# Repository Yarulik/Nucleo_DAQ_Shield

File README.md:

# Nucleo DAQ Shield
The Nucleo DAQ Shield mixed signal PCB that houses connectors and auxiliary circuitry (buffers, H-bridge, voltage regulators). It allows the STM32 microcontroller to interface with the [Analog Frontend](https://github.com/ColumbiaOpenSourceUltrasound/Analog_Frontend), motor, and other sensors.

### Drawings
Schematic:  
  
See the `drawings` folder for a high-resolution PDF version.

PCB:  
  
See the `drawings` folder for a full resolution PDF version, including each layer individually. 

3D view:  

### Bill of Materials
See `Nucleo_DAQ_Shield.html`.

### Changelog
* `v1.0` Initial design.
* `v1.2` 
* `v1.3` Changed dimensions to improve manufacturability.
* `v2.0` Replaced several components; added connector for IMU and jumpers to switch between internal/external encoder.

### Credits
Designed by William Meng and Ruoyu Sheng.

The motor control circuitry was adapted from the [Adafruit DRV8871 breakout board](https://learn.adafruit.com/adafruit-drv8871-brushed-dc-motor-driver-breakout/download).

The [Arduino Shield module](https://www.thingiverse.com/thing:9630) by nicholasclewis helped with aligning the header pins.

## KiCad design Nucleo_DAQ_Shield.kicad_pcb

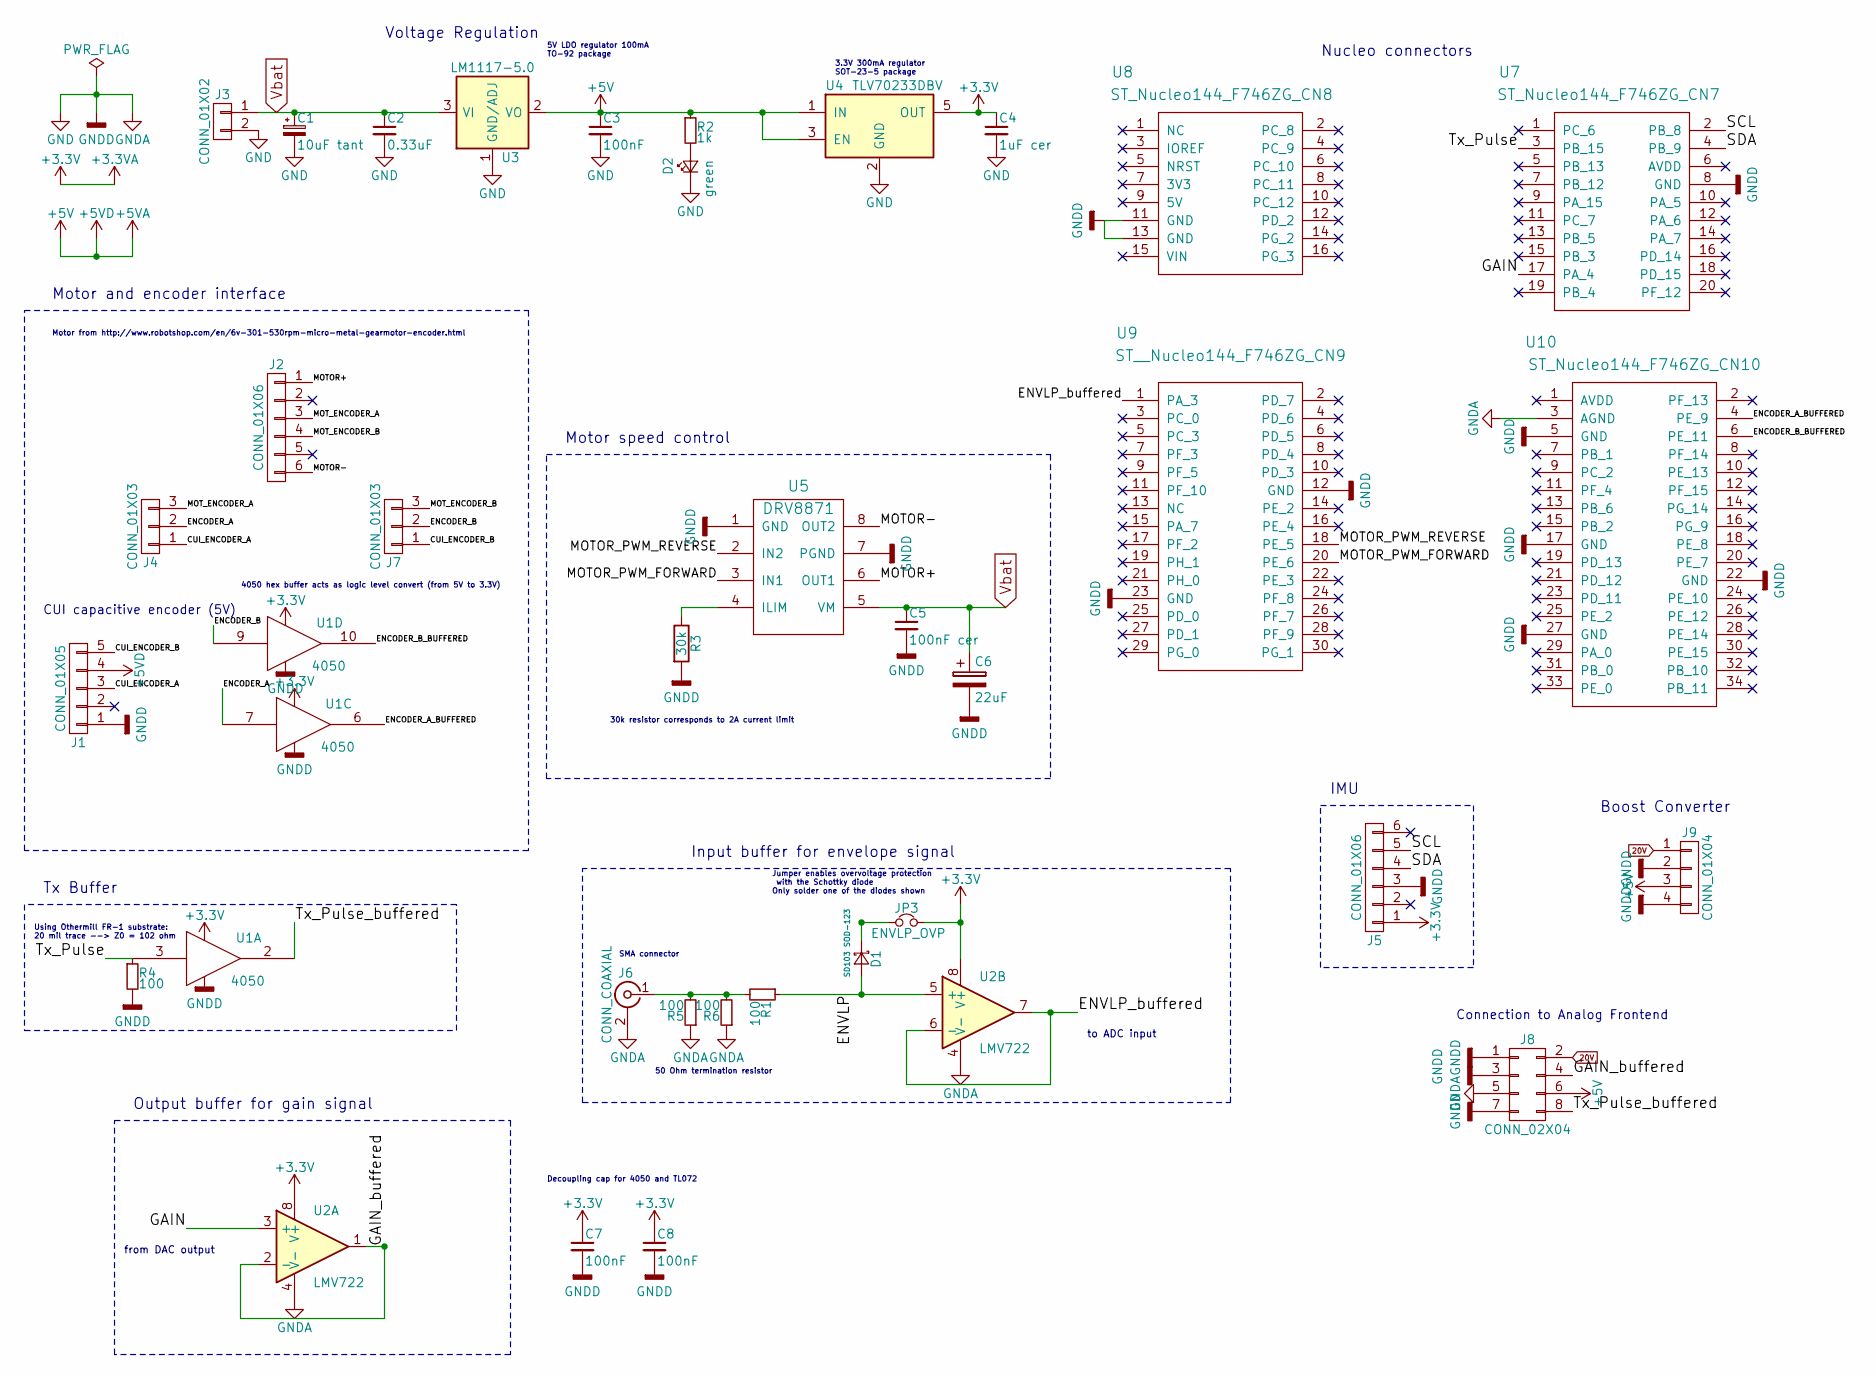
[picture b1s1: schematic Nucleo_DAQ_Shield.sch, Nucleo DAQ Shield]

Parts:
C1: 10uF tant; CP_Tantalum_Case-A_EIA-3216-18_Reflow
C2: 0.33uF; C_0603
C3, C7, C8: 100nF; C_0603
C4: 1uF cer; C_0603
C5: 100nF cer; C_0603
C6: 22uF; CP_Elec_6.3x5.8
D1: SD103 SOD-123; D_SOD-123
D2: green; LED_1206
J1: CONN_01X05; Pin_Header_Straight_1x05_Pitch2.54mm
J2, J5: CONN_01X06; Pin_Header_Straight_1x06_Pitch2.54mm
J3: CONN_01X02; Pin_Header_Straight_1x02_Pitch2.54mm
J4, J7: CONN_01X03; Pin_Header_Straight_1x03_Pitch2.54mm
J6: CONN_COAXIAL; SMA_uxcell
J8: CONN_02X04; Pin_Header_Straight_2x04_Pitch2.54mm
J9: CONN_01X04; Pin_Header_Straight_1x04_Pitch2.54mm
JP3: ENVLP_OVP; Pin_Header_Straight_1x02_Pitch2.54mm
R1, R4, R5, R6: 100; R_0805
R2: 1k; R_0805
R3: 30k; R_0805
U1: 4050; SOIC-16_3.9x9.9mm_Pitch1.27mm
U2: LMV722; SOIC-8_3.9x4.9mm_Pitch1.27mm
U3: LM1117-5.0; SOT-223
U4: TLV70233DBV; SOT-23-5
U5: DRV8871; SOIC-8_PowerPad
U7: ST_Nucleo144_F746ZG_CN7; Pin_Header_Straight_2x10_Pitch2.54mm
U8: ST_Nucleo144_F746ZG_CN8; Pin_Header_Straight_2x08_Pitch2.54mm
U9: ST__Nucleo144_F746ZG_CN9; Pin_Header_Straight_2x15_Pitch2.54mm
U10: ST_Nucleo144_F746ZG_CN10; Pin_Header_Straight_2x17_Pitch2.54mm

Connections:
20V: J8.2, J9.1
+3.3VA: C4.1, C7.1, C8.1, J5.1, JP3.2, U1.1 (VCC), U2.8 (V+), U4.5 (OUT)
+5V: C3.1, J1.4, J8.6, J9.3, R2.1, U3.2 (VO), U3.4 (VO), U4.1 (IN), U4.3 (EN)
/CUI_ENCODER_A: J1.3, J4.1
/CUI_ENCODER_B: J1.5, J7.1
/ENCODER_A: J4.2, U1.7
/ENCODER_A_BUFFERED: U1.6, U10.4 (PE_9)
/ENCODER_B: J7.2, U1.9
/ENCODER_B_BUFFERED: U1.10, U10.6 (PE_11)
/ENVLP: D1.2 (A), R1.1, U2.5 (+)
/ENVLP_buffered: U2.6 (-), U2.7, U9.1 (PA_3)
/GAIN: U2.3 (+), U7.17 (PA_4)
/GAIN_buffered: J8.4, U2.1, U2.2 (-)
/MOTOR+: J2.1, U5.6 (OUT1)
/MOTOR-: J2.6, U5.8 (OUT2)
/MOTOR_PWM_FORWARD: U5.3 (IN1), U9.20 (PE_6)
/MOTOR_PWM_REVERSE: U5.2 (IN2), U9.18 (PE_5)
/MOT_ENCODER_A: J2.3, J4.3
/MOT_ENCODER_B: J2.4, J7.3
/SCL: J5.5, U7.2 (PB_8)
/SDA: J5.4, U7.4 (PB_9)
/Tx_Pulse: R4.1, U1.3, U7.3 (PB_15)
/Tx_Pulse_buffered: J8.8, U1.2
GND: C1.2, C2.2, C3.2, C4.2, C5.2, C6.2, C7.2, C8.2, D2.1 (K), J1.1, J3.2, J5.3, J6.2 (Ext), J8.1, J8.3, J8.5, J8.7, J9.2, J9.4, R3.2, R4.2, R5.1, R6.1, U1.8 (VSS), U2.4 (V-), U3.1 (GND/ADJ), U4.2 (GND), U5.1 (GND), U5.7 (PGND), U7.8 (GND), U8.11 (GND), U8.13 (GND), U9.12 (GND), U9.23 (GND), U10.3 (AGND), U10.5 (GND), U10.17 (GND), U10.22 (GND), U10.27 (GND)
unnamed: D1.1 (K), JP3.1
unnamed: D2.2 (A), R2.2
unnamed: J6.1 (In), R1.2, R5.2, R6.2
unnamed: R3.1, U5.4 (ILIM)
Vbat: C1.1, C2.1, C5.1, C6.1, J3.1, U3.3 (VI), U5.5 (VM)

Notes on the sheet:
Output buffer for gain signal
Input buffer for envelope signal
from DAC output
to ADC input
Motor from http://www.robotshop.com/en/6v-301-530rpm-micro-metal-gearmotor-encoder.html
CUI capacitive encoder (5V)
3.3V 300mA regulator SOT-23-5 package
Motor speed control
Nucleo connectors
Jumper enables overvoltage protection with the Schottky diode Only solder one of the diodes shown
Motor and encoder interface
50 Ohm termination resistor
4050 hex buffer acts as logic level convert (from 5V to 3.3V)
30k resistor corresponds to 2A current limit
Tx Buffer
Voltage Regulation
Decoupling cap for 4050 and TL072
Using Othermill FR-1 substrate: 20 mil trace --> Z0 = 102 ohm
SMA connector
5V LDO regulator 100mA TO-92 package
IMU
Boost Converter
Connection to Analog Frontend

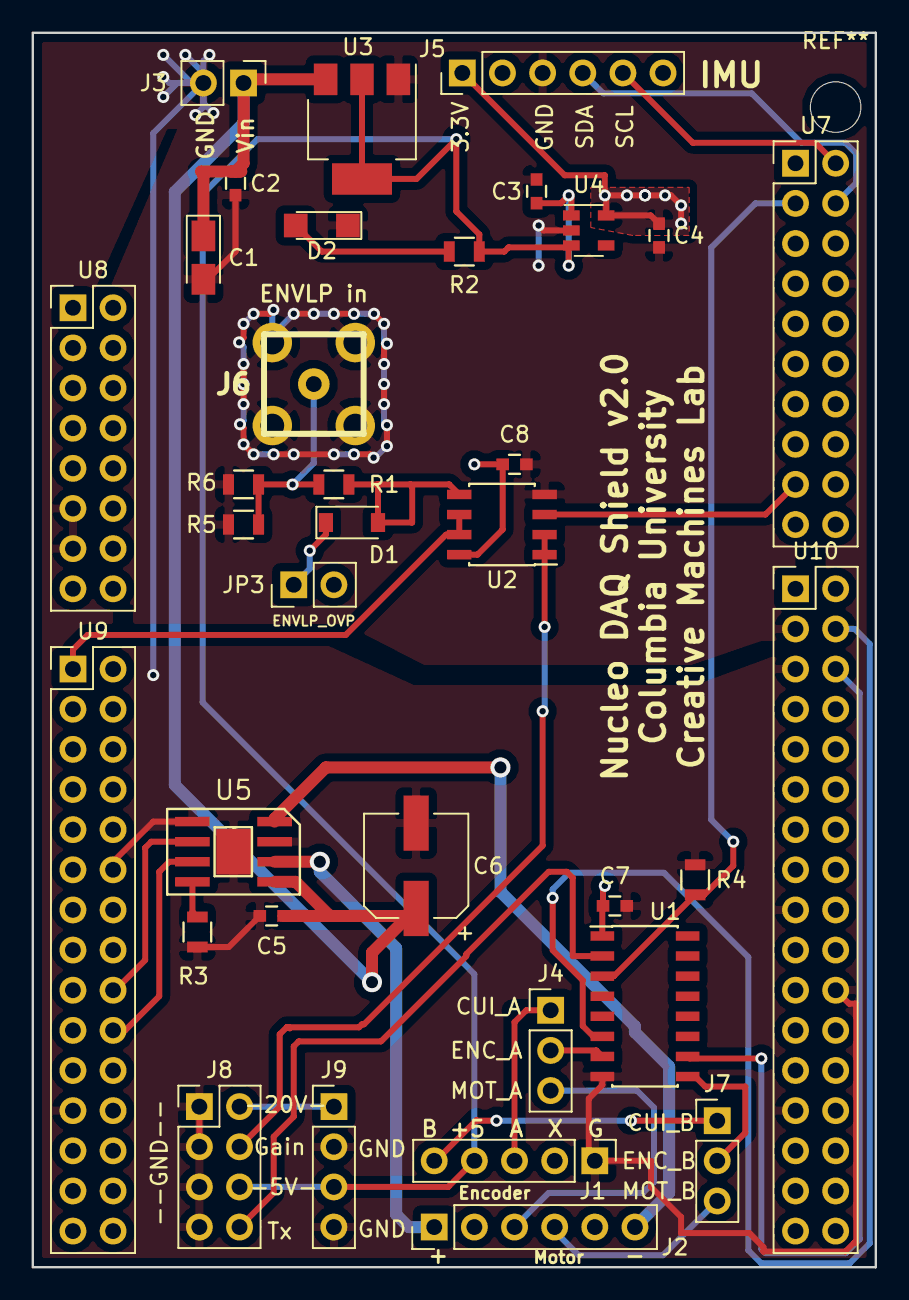
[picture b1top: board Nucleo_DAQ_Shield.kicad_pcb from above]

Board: 2 copper layers, 53.3 x 78.1 mm, 35 parts (0 on the bottom side), 29 nets.

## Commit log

2017-07-03 Started designing Nucleo DAQ Shield
2017-07-03 Added analog buffers and connection for motor/encoder
2017-07-05 Added voltage regulators and updated encoder connections
2017-07-05 Added Overvoltage Protection for envelope input buffer and jumpers to choose between motor encoder vs CUI encoder
2017-07-05 Added H-bridge for motor speed control
2017-07-07 Added reference diagram for the electrical characteristics of the ADC input
2017-07-07 Mapped out pin assignments and configurations using STM32CubeMX and generated a report file
2017-07-08 Library for Nucleo F746ZG connector symbols
2017-07-10 Added Nucleo connectors to schematic and started associating footprints
2017-07-10 Updated Nucleo connector symbols
2017-07-10 Updated Nucleo connectors in schematic
2017-07-10 --amend
2017-07-10 Reorganized schematic
2017-07-10 Associated all footprints in CvPCB
2017-07-10 Aligned connectors to Arduino shield layout
2017-07-10 Rough placement of all components
2017-07-11 Some progress on routing
2017-07-11 Mostly isolated AGND and DGND planes and fully routed analog portion; partially routed digital side
2017-07-11 Removed extraneous parts and finished PCB layout
2017-07-11 Finalized v1.0 of PCB design
2017-07-11 Gerbers and drawings for v1.0
2017-07-11 Added through hold Schottky diode as an alternative to SOD-123 Schottky diode
2017-07-11 SOIC-8 PowerPad footprint for the DRV8871 motor driver chip
2017-07-11 Nucleo DAQ Shield v1.2
2017-07-12 Added stencil file with 7mil mask to paste clearance
2017-07-12 Added BOM file
2017-07-12 Stencil now has 10mil mask to paste clearance; Nucleo header pins have been flipped in 3D view
2017-07-13 Swapped out TO-92 footprint to make it larger; refined separation between AGND and DGND
2017-07-13 Updated all vias to have at least 15 mil ring thickness
2017-07-13 Shrunk PowerPad size on the DRV8871's footprint
2017-07-13 v1.3 Gerbers
2017-07-18 BOM for Analog Frontend PCB v1.3
2017-07-20 Added silkscreen labels on Nucleo DAQ Shield PCB
2017-10-19 Analog BOM & Nucleo pins added
2017-10-25 nucleo board updated
2017-11-07 Updated IMU connector and encoder pins
2017-11-07 Q2 footprint change, connect ground plane
2017-11-08 Necleo board encoder switch
2017-11-10 SMT LED & regulator
2017-11-10 v2.0
    Fixed pin assignments for SDA and SCL
    Silkscreen labels for IMU pins
    Reorganized schematic
    Repositioned silkscreen labels to improve readability
2017-12-01 connector footprint change
2018-03-14 Added README.md
2018-03-14 Corrected header pin orientation and added v2.0 drawings.
2018-03-14 Updated README and screenshot of PCB
